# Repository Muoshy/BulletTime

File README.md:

# BulletTime
ESP32 based clock using LTP-305 led matrices.

	- NTP time retrieval
	- Brightness control
	- esp-idf
	- USB-C

## Schematic
WIP

## PCB
WIP

## Acrylic cover
WIP

## Software
Running esp-idf with esp32-wifi-manager 3.3.1 by tonyp7 for setting wifi credentials during runtime. 
Time set using sntp time example from esp-idf repository.
Brightness control using button interrupts.

## Flashing
	- Install esp-idf extension from Visual Studio Code marketplace
	- Open LTP_clock folder from VSCode
	- Select port, compile & flash.

## BOM

| Component                		| Quantity 	| Description 						|
|--------------------------		|----------	|------								|
| ESP32-WROOM-32D              	| 1x 		| ESP32     						|
| CP2102N-A02-GQFN24            | 1x       	| USB-UART     						|
| HT16K33			| 2x		| LED driver |
| LDL1117            			| 1x       	| Voltage regulator     			|
| SP0503BAHTG				   	| 1x       	| ESD-protection     				|
| LTP-305					   	| 6x       	| 5x7 led matrix     				|
| PCA9306					   	| 1x       	| I2C level shifter     			|
| 5.2x5.2mm SMD pushbutton 		| 4x       	| Pushbutton						|
| 14 Position DIP socket        | 6x       	|      								|
| Resistors (WIP)        		|        	|      								|
| Capacitors (WIP)        		|        	|      								|

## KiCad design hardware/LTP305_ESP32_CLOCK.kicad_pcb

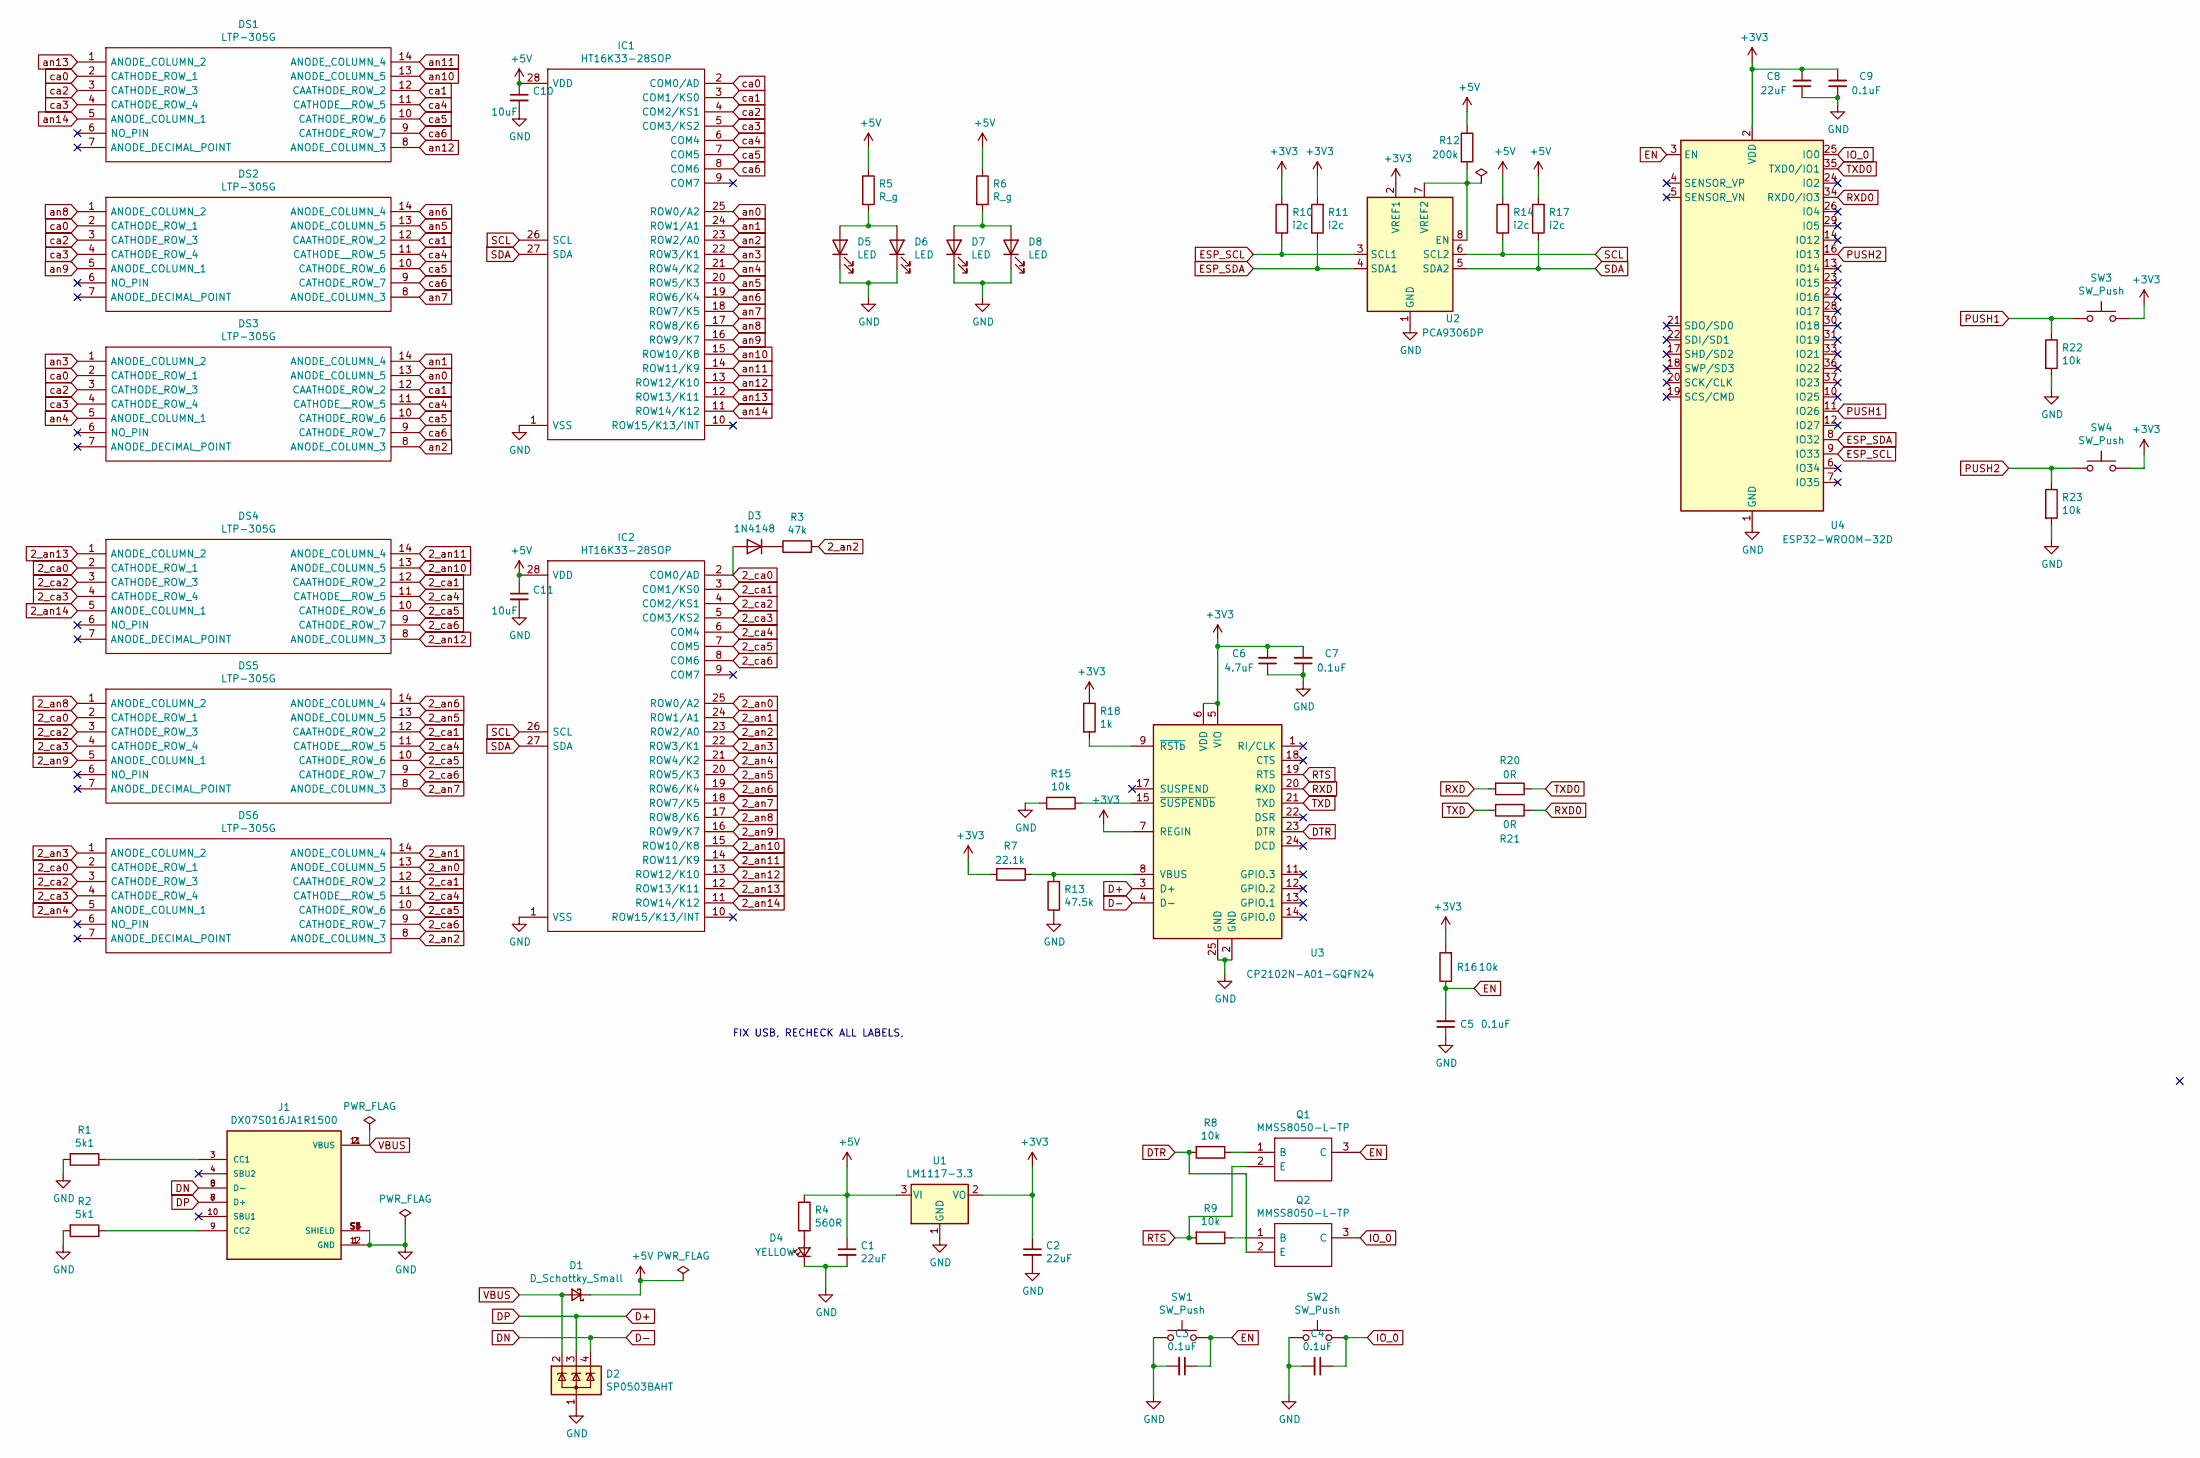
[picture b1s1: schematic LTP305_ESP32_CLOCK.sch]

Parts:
C1, C2, C8: 22uF; C_0603_1608Metric
C3, C4, C5, C7, C9: 0.1uF; C_0603_1608Metric
C6: 4.7uF; C_0603_1608Metric
C10, C11: 10uF; C_0603_1608Metric
D1: D_Schottky_Small; D_SOD-123
D2: SP0503BAHT; SOT-143
D3: 1N4148; D_SOD-123
D4: YELLOW; LED_1206_3216Metric_Castellated
D5, D6, D7, D8: LED; LED_0603_1608Metric_Pad1.05x0.95mm_HandSolder
DS1, DS2, DS3, DS4, DS5, DS6: LTP-305G; DIPS762W50P254L1850H400Q14N; Mouser Part Number 859-LTP-305G
IC1, IC2: HT16K33-28SOP; SOIC127P1031X264-28N; Manufacturer_Part_Number HT16K33-28SOP
J1: DX07S016JA1R1500; JAE_DX07S016JA1R1500; PARTREV 1
Q1, Q2: MMSS8050-L-TP; SOT96P237X122-3N; Mouser Part Number 833-MMSS8050-L-TP
R1, R2: 5k1; R_0603_1608Metric
R3: 47k; R_0603_1608Metric
R4: 560R; R_0603_1608Metric
R5, R6: R_g; R_0805_2012Metric_Pad1.20x1.40mm_HandSolder
R7: 22.1k; R_0603_1608Metric
R8, R9, R15, R16, R22, R23: 10k; R_0603_1608Metric
R10, R11: i2c; R_0603_1608Metric
R12: 200k; R_0603_1608Metric
R13: 47.5k; R_0603_1608Metric
R14, R17: i2c; R_0805_2012Metric_Pad1.20x1.40mm_HandSolder
R18: 1k; R_0603_1608Metric
R20, R21: 0R; R_0603_1608Metric
SW1, SW2, SW3, SW4: SW_Push; SW_SPST_SKQG_WithStem
U1: LM1117-3.3; SOT-223
U2: PCA9306DP; TSSOP-8_3x3mm_P0.65mm
U3: CP2102N-A01-GQFN24; QFN-24-1EP_4x4mm_P0.5mm_EP2.6x2.6mm
U4: ESP32-WROOM-32D; ESP32-WROOM-32

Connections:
2_an0: DS6.13 (ANODE_COLUMN_5), IC2.25 (ROW0/A2)
2_an1: DS6.14 (ANODE_COLUMN_4), IC2.24 (ROW1/A1)
2_an2: DS6.8 (ANODE_COLUMN_3), IC2.23 (ROW2/A0), R3.2
2_an3: DS6.1 (ANODE_COLUMN_2), IC2.22 (ROW3/K1)
2_an4: DS6.5 (ANODE_COLUMN_1), IC2.21 (ROW4/K2)
2_an5: DS5.13 (ANODE_COLUMN_5), IC2.20 (ROW5/K3)
2_an6: DS5.14 (ANODE_COLUMN_4), IC2.19 (ROW6/K4)
2_an7: DS5.8 (ANODE_COLUMN_3), IC2.18 (ROW7/K5)
2_an8: DS5.1 (ANODE_COLUMN_2), IC2.17 (ROW8/K6)
2_an9: DS5.5 (ANODE_COLUMN_1), IC2.16 (ROW9/K7)
2_an10: DS4.13 (ANODE_COLUMN_5), IC2.15 (ROW10/K8)
2_an11: DS4.14 (ANODE_COLUMN_4), IC2.14 (ROW11/K9)
2_an12: DS4.8 (ANODE_COLUMN_3), IC2.13 (ROW12/K10)
2_an13: DS4.1 (ANODE_COLUMN_2), IC2.12 (ROW13/K11)
2_an14: DS4.5 (ANODE_COLUMN_1), IC2.11 (ROW14/K12)
2_ca0: D3.2 (A), DS4.2 (CATHODE_ROW_1), DS5.2 (CATHODE_ROW_1), DS6.2 (CATHODE_ROW_1), IC2.2 (COM0/AD)
2_ca1: DS4.12 (CAATHODE_ROW_2), DS5.12 (CAATHODE_ROW_2), DS6.12 (CAATHODE_ROW_2), IC2.3 (COM1/KS0)
2_ca2: DS4.3 (CATHODE_ROW_3), DS5.3 (CATHODE_ROW_3), DS6.3 (CATHODE_ROW_3), IC2.4 (COM2/KS1)
2_ca3: DS4.4 (CATHODE_ROW_4), DS5.4 (CATHODE_ROW_4), DS6.4 (CATHODE_ROW_4), IC2.5 (COM3/KS2)
2_ca4: DS4.11 (CATHODE__ROW_5), DS5.11 (CATHODE__ROW_5), DS6.11 (CATHODE__ROW_5), IC2.6 (COM4)
2_ca5: DS4.10 (CATHODE_ROW_6), DS5.10 (CATHODE_ROW_6), DS6.10 (CATHODE_ROW_6), IC2.7 (COM5)
2_ca6: DS4.9 (CATHODE_ROW_7), DS5.9 (CATHODE_ROW_7), DS6.9 (CATHODE_ROW_7), IC2.8 (COM6)
+3V3: C2.1, C6.2, C7.2, C8.2, C9.2, R7.2, R10.2, R11.2, R16.2, R18.1, SW3.2, SW4.2, U1.2 (VO), U1.4, U2.2 (VREF1), U3.5 (VIO), U3.6 (VDD), U3.7 (REGIN), U4.2 (VDD); also elsewhere on the board
+5V: C1.1, C10.1, C11.1, D1.1 (K), IC1.28 (VDD), IC2.28 (VDD), R4.1, R5.1, R6.1, R12.1, R14.2, R17.2, U1.3 (VI)
D+: D2.3 (K), J1.6 (D+), J1.7 (D+), U3.3 (D+)
D-: D2.4 (K), J1.5 (D-), J1.8 (D-), U3.4 (D-)
DTR: Q2.2 (E), R8.2, U3.23 (DTR)
EN: C3.1, C5.2, Q1.3 (C), R16.1, SW1.2, U4.3 (EN); also elsewhere on the board
ESP_SCL: R10.1, U2.3 (SCL1), U4.9 (IO33)
ESP_SDA: R11.1, U2.4 (SDA1), U4.8 (IO32)
GND: C1.2, C2.2, C3.2, C4.2, C5.1, C6.1, C7.1, C8.1, C9.1, C10.2, C11.2, D2.1 (A), D4.1 (K), D5.1 (K), D6.1 (K), D7.1 (K), D8.1 (K), IC1.1 (VSS), IC2.1 (VSS), J1.1 (GND), J1.12 (GND), J1.S1 (SHIELD), J1.S2 (SHIELD), J1.S3 (SHIELD), J1.S4 (SHIELD), J1.S5 (SHIELD), J1.S6 (SHIELD), R1.2, R2.2, R13.1, R15.2, R22.2, R23.2, SW1.1, SW2.1, U1.1 (GND), U2.1 (GND), U3.2 (GND), U3.25 (GND), U4.1 (GND), U4.15 (GND), U4.38 (GND), U4.39 (GND); also elsewhere on the board
IO_0: C4.1, Q2.3 (C), SW2.2, U4.25 (IO0); also elsewhere on the board
unnamed: D3.1 (K), R3.1
unnamed: D4.2 (A), R4.2
unnamed: D5.2 (A), D6.2 (A), R5.2
unnamed: D7.2 (A), D8.2 (A), R6.2
unnamed: J1.3 (CC1), R1.1
unnamed: J1.9 (CC2), R2.1
unnamed: Q1.1 (B), R8.1
unnamed: Q2.1 (B), R9.1
unnamed: R12.2, U2.7 (VREF2), U2.8 (EN)
unnamed: R7.1, R13.2, U3.8 (VBUS)
unnamed: R15.1, U3.15 (~SUSPENDb)
unnamed: R18.2, U3.9 (~RSTb)
PUSH1: R22.1, SW3.1, U4.11 (IO26); also elsewhere on the board
PUSH2: R23.1, SW4.1, U4.16 (IO13); also elsewhere on the board
RTS: Q1.2 (E), R9.2, U3.19 (RTS)
RXD: R20.2, U3.20 (RXD)
RXD0: R21.1, U4.34 (RXD0/IO3)
SCL: IC1.26 (SCL), IC2.26 (SCL), R14.1, U2.6 (SCL2)
SDA: IC1.27 (SDA), IC2.27 (SDA), R17.1, U2.5 (SDA2)
TXD: R21.2, U3.21 (TXD)
TXD0: R20.1, U4.35 (TXD0/IO1)
VBUS: D1.2 (A), D2.2 (K), J1.2 (VBUS), J1.11 (VBUS)
an0: DS3.13 (ANODE_COLUMN_5), IC1.25 (ROW0/A2)
an1: DS3.14 (ANODE_COLUMN_4), IC1.24 (ROW1/A1)
an2: DS3.8 (ANODE_COLUMN_3), IC1.23 (ROW2/A0)
an3: DS3.1 (ANODE_COLUMN_2), IC1.22 (ROW3/K1)
an4: DS3.5 (ANODE_COLUMN_1), IC1.21 (ROW4/K2)
an5: DS2.13 (ANODE_COLUMN_5), IC1.20 (ROW5/K3)
an6: DS2.14 (ANODE_COLUMN_4), IC1.19 (ROW6/K4)
an7: DS2.8 (ANODE_COLUMN_3), IC1.18 (ROW7/K5)
an8: DS2.1 (ANODE_COLUMN_2), IC1.17 (ROW8/K6)
an9: DS2.5 (ANODE_COLUMN_1), IC1.16 (ROW9/K7)
an10: DS1.13 (ANODE_COLUMN_5), IC1.15 (ROW10/K8)
an11: DS1.14 (ANODE_COLUMN_4), IC1.14 (ROW11/K9)
an12: DS1.8 (ANODE_COLUMN_3), IC1.13 (ROW12/K10)
an13: DS1.1 (ANODE_COLUMN_2), IC1.12 (ROW13/K11)
an14: DS1.5 (ANODE_COLUMN_1), IC1.11 (ROW14/K12)
ca0: DS1.2 (CATHODE_ROW_1), DS2.2 (CATHODE_ROW_1), DS3.2 (CATHODE_ROW_1), IC1.2 (COM0/AD)
ca1: DS1.12 (CAATHODE_ROW_2), DS2.12 (CAATHODE_ROW_2), DS3.12 (CAATHODE_ROW_2), IC1.3 (COM1/KS0)
ca2: DS1.3 (CATHODE_ROW_3), DS2.3 (CATHODE_ROW_3), DS3.3 (CATHODE_ROW_3), IC1.4 (COM2/KS1)
ca3: DS1.4 (CATHODE_ROW_4), DS2.4 (CATHODE_ROW_4), DS3.4 (CATHODE_ROW_4), IC1.5 (COM3/KS2)
ca4: DS1.11 (CATHODE__ROW_5), DS2.11 (CATHODE__ROW_5), DS3.11 (CATHODE__ROW_5), IC1.6 (COM4)
ca5: DS1.10 (CATHODE_ROW_6), DS2.10 (CATHODE_ROW_6), DS3.10 (CATHODE_ROW_6), IC1.7 (COM5)
ca6: DS1.9 (CATHODE_ROW_7), DS2.9 (CATHODE_ROW_7), DS3.9 (CATHODE_ROW_7), IC1.8 (COM6)

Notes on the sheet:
FIX USB, RECHECK ALL LABELS,

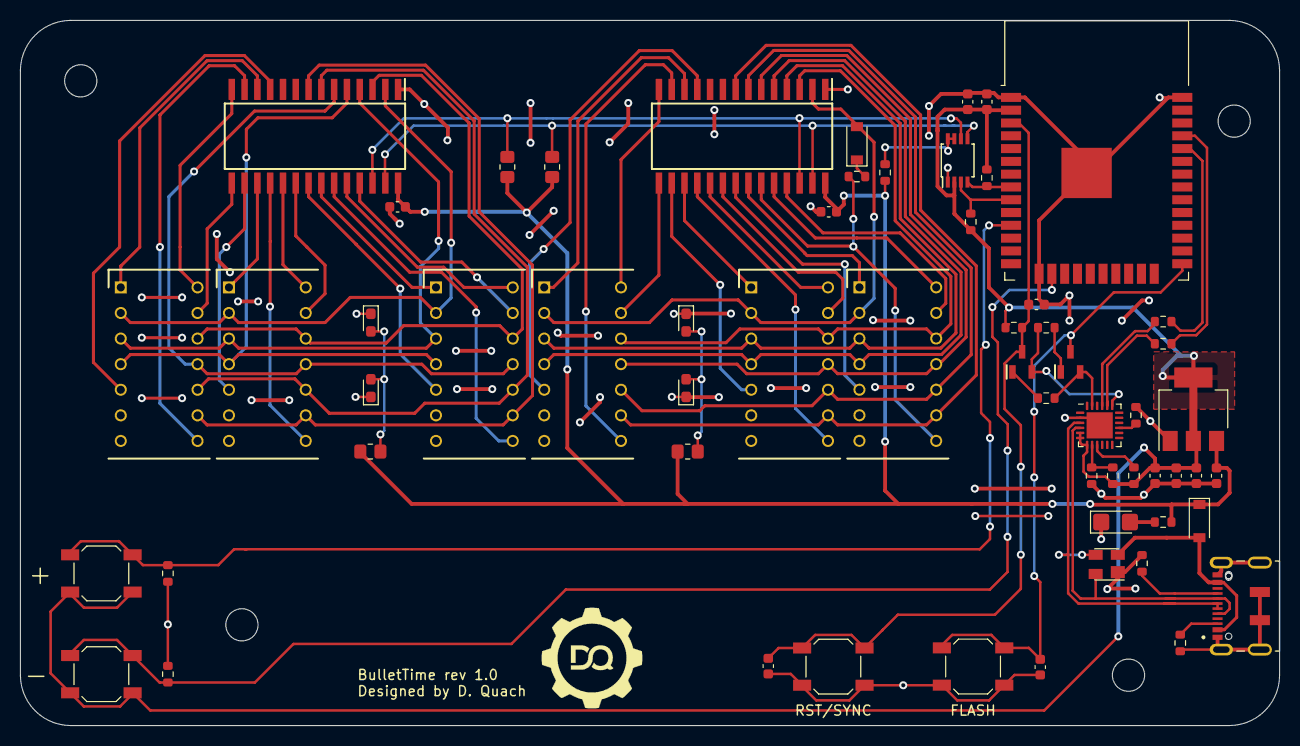
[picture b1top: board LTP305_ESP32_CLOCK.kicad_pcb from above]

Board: 2 copper layers, 125.0 x 70.0 mm, 60 parts (0 on the bottom side), 76 nets.

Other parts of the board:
+: SW_Push; SW_SPST_SKQG_WithStem
-: SW_Push; SW_SPST_SKQG_WithStem
FLASH: SW_Push; SW_SPST_SKQG_WithStem
RST/SYNC: SW_Push; SW_SPST_SKQG_WithStem

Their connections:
+3V3: +.2, -.2; also elsewhere on the board
EN: RST/SYNC.2; also elsewhere on the board
GND: FLASH.1, RST/SYNC.1; also elsewhere on the board
IO_0: FLASH.2; also elsewhere on the board
PUSH1: +.1; also elsewhere on the board
PUSH2: -.1; also elsewhere on the board

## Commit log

2021-03-21 added software
2021-03-21 added image of frontside for both colors
2021-03-21 rotated image
2021-03-21 cropped img
2021-04-30 added kicad files
